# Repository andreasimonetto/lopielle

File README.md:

Lopielle
========

MIDI synth based on Yamaha OPLL FM synthesis sound chip (YM2413).

Made with KiCad, MPLAB-X, Inkscape, The GIMP.

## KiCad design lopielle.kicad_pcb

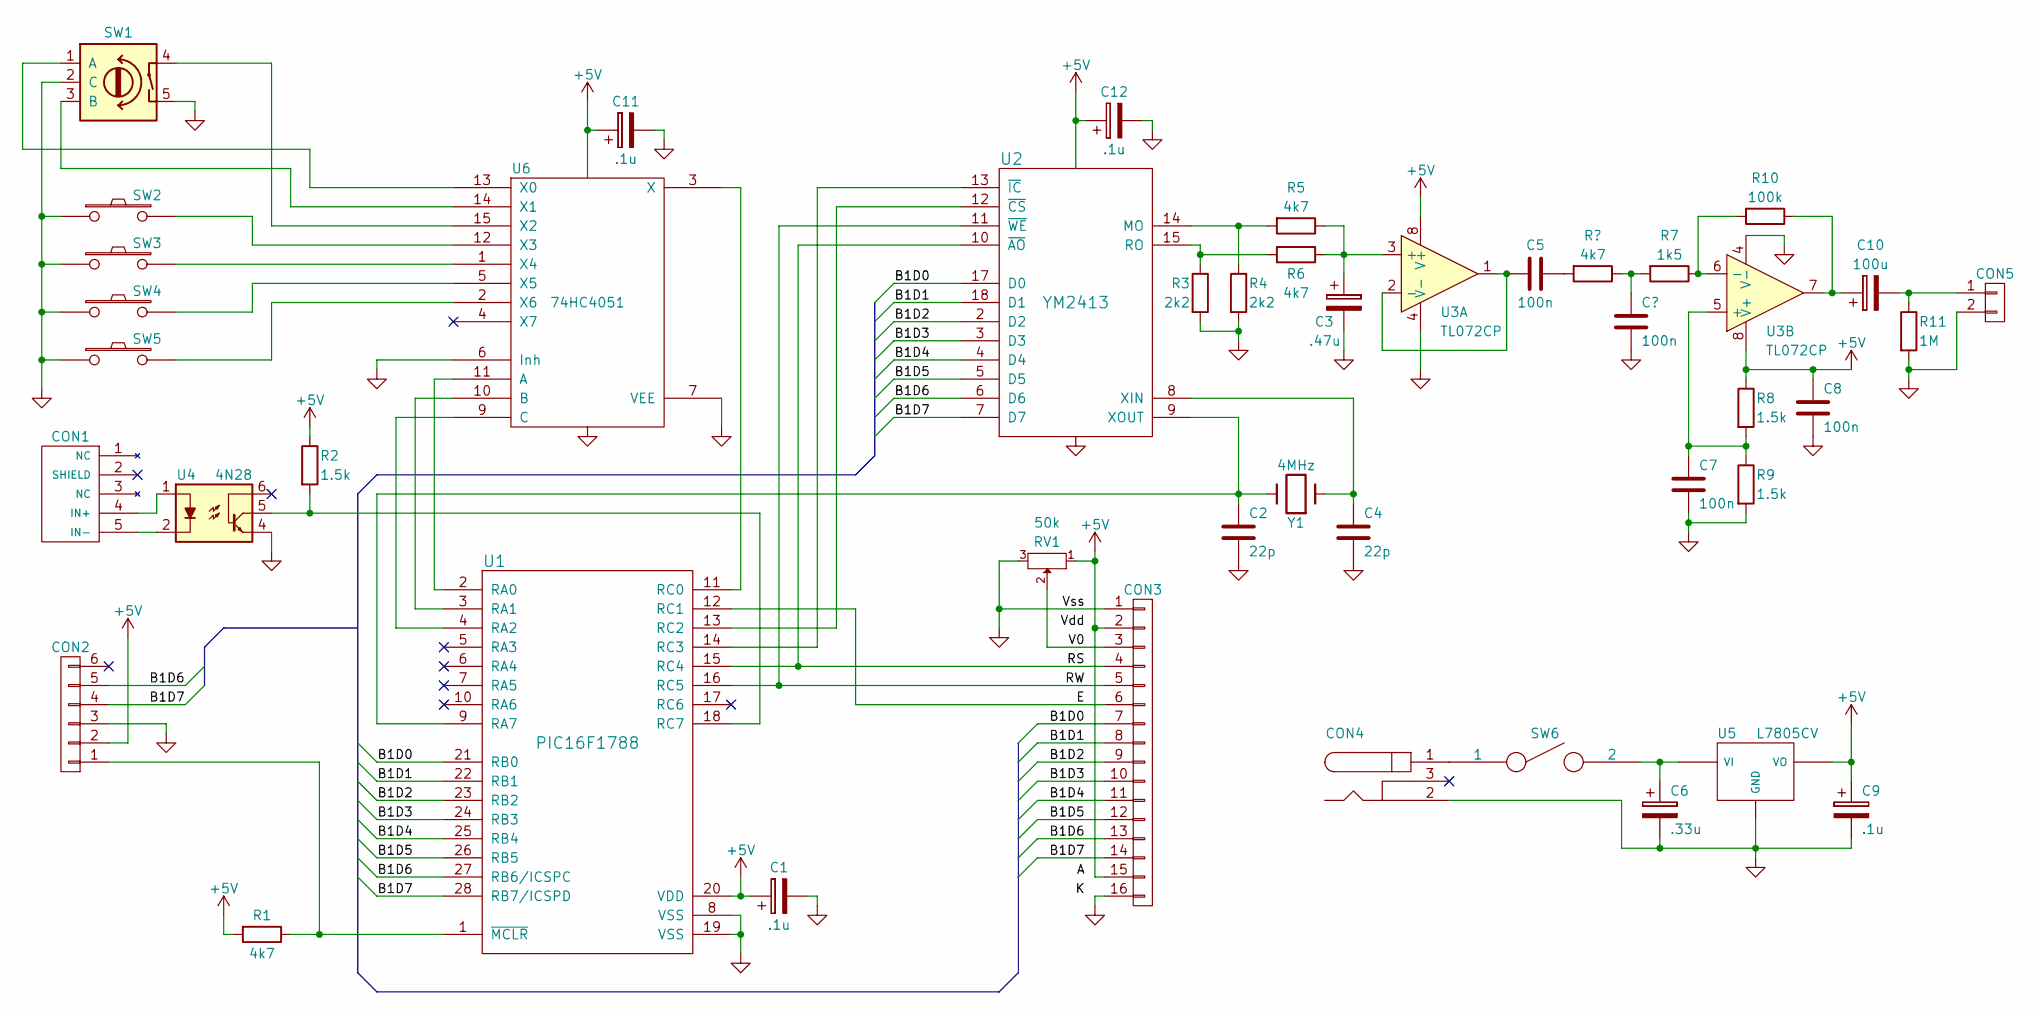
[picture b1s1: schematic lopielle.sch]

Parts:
C1, C9, C11, C12: .1u; C_Radial_D5_L11_P2.5
C2, C4: 22p; C_Disc_D6_P5
C3: .47u; C_Radial_D5_L11_P2.5
C5, C7, C8: 100n; C_Disc_D3_P2.5
C6: .33u; C_Radial_D5_L11_P2.5
C10: 100u; C_Radial_D5_L11_P2.5
CON1: MIDI_In; G9820_SX
CON2: CONN_01X06; PINHEAD1-6
CON3: CONN_01X16; Pin_Header_Straight_1x16
CON4: BARREL_JACK; G10560
CON5: CONN_01X02; Pin_Header_Straight_1x02
R1, R5, R6: 4k7; Resistor_Horizontal_RM7mm
R2, R8, R9: 1.5k; Resistor_Horizontal_RM7mm
R3, R4: 2k2; Resistor_Horizontal_RM7mm
R7: 1k5; Resistor_Horizontal_RM7mm
R10: 100k; Resistor_Horizontal_RM7mm
R11: 1M; Resistor_Horizontal_RM7mm
RV1: 50k; Trimmer_ACP
SW1: Rotary_Encoder_Switch; PEC12R-4222F-S0024
SW2, SW3, SW4, SW5: SW_PUSH; SW_PUSH_SMALL
SW6: SPST; Switch_DPDT
U1: PIC16F1788; DIP-28_W7.62mm
U2: YM2413; DIP-18_W7.62mm
U3: TL072CP; DIP-8_W7.62mm
U4: 4N28; DIP-6_W7.62mm
U5: L7805CV; TO-220_Neutral123_Vertical
U6: 74HC4051; DIP-16_W7.62mm
Y1: 4MHz; Crystal_HC49-U_Vertical

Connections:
+5V: C1.1, C8.1, C9.1, C11.1, C12.1, CON2.2, CON3.2, CON3.15, R1.2, R2.1, R8.1, RV1.1, U1.20 (VDD), U2.16 (VCC), U3.8 (V+), U5.3 (VO), U6.16 (VDD)
/B1D0: CON3.7, U1.21 (RB0), U2.17 (D0)
/B1D1: CON3.8, U1.22 (RB1), U2.18 (D1)
/B1D2: CON3.9, U1.23 (RB2), U2.2 (D2)
/B1D3: CON3.10, U1.24 (RB3), U2.3 (D3)
/B1D4: CON3.11, U1.25 (RB4), U2.4 (D4)
/B1D5: CON3.12, U1.26 (RB5), U2.5 (D5)
/B1D6: CON2.5, CON3.13, U1.27 (RB6/ICSPC), U2.6 (D6)
/B1D7: CON2.4, CON3.14, U1.28 (RB7/ICSPD), U2.7 (D7)
/E: CON3.6, U1.12 (RC1)
/RS: CON3.4, U1.15 (RC4), U2.10 (~AO)
/RW: CON3.5, U1.16 (RC5), U2.11 (~WE)
/V0: CON3.3, RV1.2
GND: C1.2, C2.2, C3.2, C4.2, C6.2, C7.2, C8.2, C9.2, C11.2, C12.2, CON2.3, CON3.1, CON3.16, CON4.2, CON5.2, R3.2, R4.2, R9.2, R11.2, RV1.3, SW1.2 (C), SW1.5, SW2.1, SW3.1, SW4.1, SW5.1, U1.8 (VSS), U1.19 (VSS), U2.1 (GND), U3.4 (V-), U4.4, U5.2 (GND), U6.6 (Inh), U6.7 (VEE), U6.8 (VSS)
unnamed: C2.1, U1.9 (RA7), U2.9 (XOUT), Y1.2
unnamed: C3.1, R5.1, R6.1, U3.3 (+)
unnamed: C4.1, U2.8 (XIN), Y1.1
unnamed: C5.1, R7.2
unnamed: C5.2, U3.1, U3.2 (-)
unnamed: C6.1, SW6.2, U5.1 (VI)
unnamed: C7.1, R8.2, R9.1, U3.5 (+)
unnamed: C10.1, R10.1, U3.7
unnamed: C10.2, CON5.1, R11.1
unnamed: CON1.4 (IN+), U4.1
unnamed: CON1.5 (IN-), U4.2
unnamed: CON2.1, R1.1, U1.1 (~MCLR)
unnamed: CON4.1, SW6.1
unnamed: R2.2, U1.18 (RC7), U4.5
unnamed: R3.1, R6.2, U2.15 (RO)
unnamed: R4.1, R5.2, U2.14 (MO)
unnamed: R7.1, R10.2, U3.6 (-)
unnamed: SW1.1 (A), U6.13 (X0)
unnamed: SW1.3 (B), U6.14 (X1)
unnamed: SW1.4, U6.15 (X2)
unnamed: SW2.2, U6.12 (X3)
unnamed: SW3.2, U6.1 (X4)
unnamed: SW4.2, U6.5 (X5)
unnamed: SW5.2, U6.2 (X6)
unnamed: U1.2 (RA0), U6.11 (A)
unnamed: U1.3 (RA1), U6.10 (B)
unnamed: U1.4 (RA2), U6.9 (C)
unnamed: U1.11 (RC0), U6.3 (X)
unnamed: U1.13 (RC2), U2.12 (~CS)
unnamed: U1.14 (RC3), U2.13 (~IC)

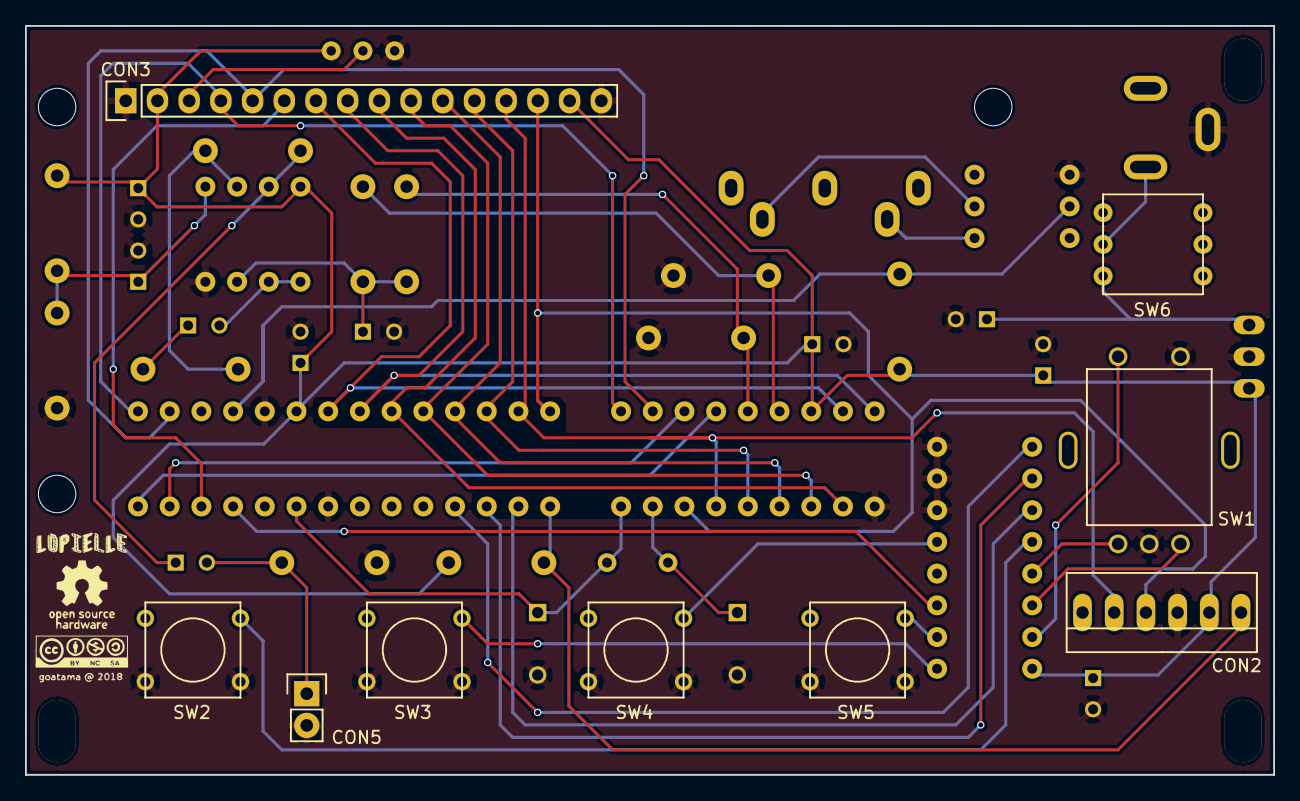
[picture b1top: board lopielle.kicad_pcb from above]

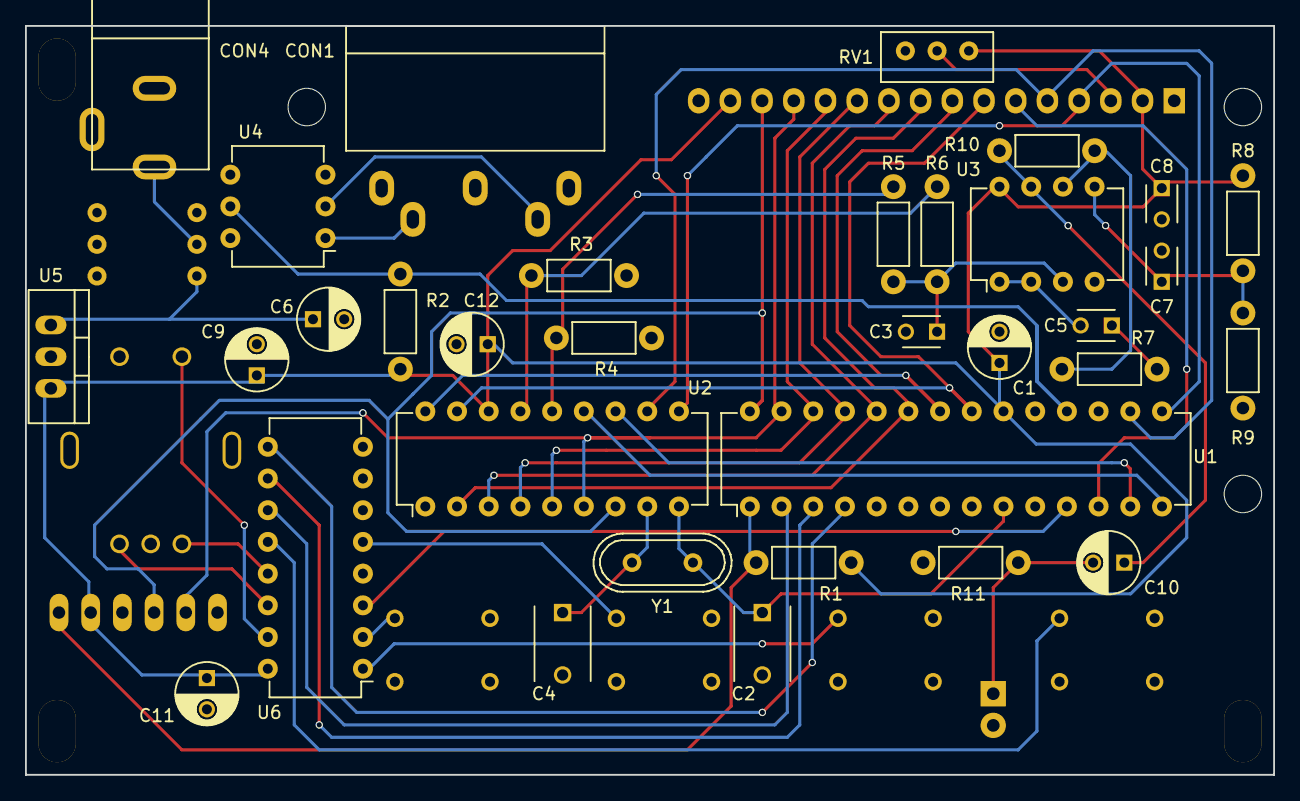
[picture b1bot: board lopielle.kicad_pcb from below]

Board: 2 copper layers, 100.0 x 60.0 mm, 42 parts (33 on the bottom side), 44 nets.

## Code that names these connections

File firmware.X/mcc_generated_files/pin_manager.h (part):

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// get/set CTL_A0 aliases
#define CTL_A0_TRIS                 TRISAbits.TRISA0
#define CTL_A0_LAT                  LATAbits.LATA0
#define CTL_A0_PORT                 PORTAbits.RA0
#define CTL_A0_WPU                  WPUAbits.WPUA0
#define CTL_A0_ANS                  ANSELAbits.ANSA0
#define CTL_A0_SetHigh()            do { LATAbits.LATA0 = 1; } while(0)
#define CTL_A0_SetLow()             do { LATAbits.LATA0 = 0; } while(0)
#define CTL_A0_Toggle()             do { LATAbits.LATA0 = ~LATAbits.LATA0; } while(0)
#define CTL_A0_GetValue()           PORTAbits.RA0
#define CTL_A0_SetDigitalInput()    do { TRISAbits.TRISA0 = 1; } while(0)
#define CTL_A0_SetDigitalOutput()   do { TRISAbits.TRISA0 = 0; } while(0)
#define CTL_A0_SetPullup()          do { WPUAbits.WPUA0 = 1; } while(0)
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// get/set CTL_A1 aliases
#define CTL_A1_TRIS                 TRISAbits.TRISA1
#define CTL_A1_LAT                  LATAbits.LATA1
#define CTL_A1_PORT                 PORTAbits.RA1
#define CTL_A1_WPU                  WPUAbits.WPUA1
#define CTL_A1_ANS                  ANSELAbits.ANSA1
#define CTL_A1_SetHigh()            do { LATAbits.LATA1 = 1; } while(0)
#define CTL_A1_SetLow()             do { LATAbits.LATA1 = 0; } while(0)
#define CTL_A1_Toggle()             do { LATAbits.LATA1 = ~LATAbits.LATA1; } while(0)
#define CTL_A1_GetValue()           PORTAbits.RA1
#define CTL_A1_SetDigitalInput()    do { TRISAbits.TRISA1 = 1; } while(0)
#define CTL_A1_SetDigitalOutput()   do { TRISAbits.TRISA1 = 0; } while(0)
#define CTL_A1_SetPullup()          do { WPUAbits.WPUA1 = 1; } while(0)
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// get/set CTL_A2 aliases
#define CTL_A2_TRIS                 TRISAbits.TRISA2
#define CTL_A2_LAT                  LATAbits.LATA2
#define CTL_A2_PORT                 PORTAbits.RA2
#define CTL_A2_WPU                  WPUAbits.WPUA2
#define CTL_A2_ANS                  ANSELAbits.ANSA2
#define CTL_A2_SetHigh()            do { LATAbits.LATA2 = 1; } while(0)
#define CTL_A2_SetLow()             do { LATAbits.LATA2 = 0; } while(0)
#define CTL_A2_Toggle()             do { LATAbits.LATA2 = ~LATAbits.LATA2; } while(0)
#define CTL_A2_GetValue()           PORTAbits.RA2
#define CTL_A2_SetDigitalInput()    do { TRISAbits.TRISA2 = 1; } while(0)
#define CTL_A2_SetDigitalOutput()   do { TRISAbits.TRISA2 = 0; } while(0)
#define CTL_A2_SetPullup()          do { WPUAbits.WPUA2 = 1; } while(0)
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// get/set D0 aliases
#define D0_TRIS                 TRISBbits.TRISB0
#define D0_LAT                  LATBbits.LATB0
#define D0_PORT                 PORTBbits.RB0
#define D0_WPU                  WPUBbits.WPUB0
#define D0_ANS                  ANSELBbits.ANSB0
#define D0_SetHigh()            do { LATBbits.LATB0 = 1; } while(0)
#define D0_SetLow()             do { LATBbits.LATB0 = 0; } while(0)
#define D0_Toggle()             do { LATBbits.LATB0 = ~LATBbits.LATB0; } while(0)
#define D0_GetValue()           PORTBbits.RB0
#define D0_SetDigitalInput()    do { TRISBbits.TRISB0 = 1; } while(0)
#define D0_SetDigitalOutput()   do { TRISBbits.TRISB0 = 0; } while(0)
#define D0_SetPullup()          do { WPUBbits.WPUB0 = 1; } while(0)
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// get/set D1 aliases
#define D1_TRIS                 TRISBbits.TRISB1
#define D1_LAT                  LATBbits.LATB1
#define D1_PORT                 PORTBbits.RB1
#define D1_WPU                  WPUBbits.WPUB1
#define D1_ANS                  ANSELBbits.ANSB1
#define D1_SetHigh()            do { LATBbits.LATB1 = 1; } while(0)
#define D1_SetLow()             do { LATBbits.LATB1 = 0; } while(0)
#define D1_Toggle()             do { LATBbits.LATB1 = ~LATBbits.LATB1; } while(0)
#define D1_GetValue()           PORTBbits.RB1
#define D1_SetDigitalInput()    do { TRISBbits.TRISB1 = 1; } while(0)
#define D1_SetDigitalOutput()   do { TRISBbits.TRISB1 = 0; } while(0)
#define D1_SetPullup()          do { WPUBbits.WPUB1 = 1; } while(0)
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// get/set D2 aliases
#define D2_TRIS                 TRISBbits.TRISB2
#define D2_LAT                  LATBbits.LATB2
#define D2_PORT                 PORTBbits.RB2
#define D2_WPU                  WPUBbits.WPUB2
#define D2_ANS                  ANSELBbits.ANSB2
#define D2_SetHigh()            do { LATBbits.LATB2 = 1; } while(0)
#define D2_SetLow()             do { LATBbits.LATB2 = 0; } while(0)
#define D2_Toggle()             do { LATBbits.LATB2 = ~LATBbits.LATB2; } while(0)
#define D2_GetValue()           PORTBbits.RB2
#define D2_SetDigitalInput()    do { TRISBbits.TRISB2 = 1; } while(0)
#define D2_SetDigitalOutput()   do { TRISBbits.TRISB2 = 0; } while(0)
#define D2_SetPullup()          do { WPUBbits.WPUB2 = 1; } while(0)
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// get/set D3 aliases
#define D3_TRIS                 TRISBbits.TRISB3
#define D3_LAT                  LATBbits.LATB3
#define D3_PORT                 PORTBbits.RB3
#define D3_WPU                  WPUBbits.WPUB3
#define D3_ANS                  ANSELBbits.ANSB3
#define D3_SetHigh()            do { LATBbits.LATB3 = 1; } while(0)
#define D3_SetLow()             do { LATBbits.LATB3 = 0; } while(0)
#define D3_Toggle()             do { LATBbits.LATB3 = ~LATBbits.LATB3; } while(0)
#define D3_GetValue()           PORTBbits.RB3
#define D3_SetDigitalInput()    do { TRISBbits.TRISB3 = 1; } while(0)
#define D3_SetDigitalOutput()   do { TRISBbits.TRISB3 = 0; } while(0)
#define D3_SetPullup()          do { WPUBbits.WPUB3 = 1; } while(0)
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// get/set D4 aliases
#define D4_TRIS                 TRISBbits.TRISB4
#define D4_LAT                  LATBbits.LATB4
#define D4_PORT                 PORTBbits.RB4
#define D4_WPU                  WPUBbits.WPUB4
#define D4_ANS                  ANSELBbits.ANSB4
#define D4_SetHigh()            do { LATBbits.LATB4 = 1; } while(0)
#define D4_SetLow()             do { LATBbits.LATB4 = 0; } while(0)
#define D4_Toggle()             do { LATBbits.LATB4 = ~LATBbits.LATB4; } while(0)
#define D4_GetValue()           PORTBbits.RB4
#define D4_SetDigitalInput()    do { TRISBbits.TRISB4 = 1; } while(0)
#define D4_SetDigitalOutput()   do { TRISBbits.TRISB4 = 0; } while(0)
#define D4_SetPullup()          do { WPUBbits.WPUB4 = 1; } while(0)
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// get/set D5 aliases
#define D5_TRIS                 TRISBbits.TRISB5
#define D5_LAT                  LATBbits.LATB5
#define D5_PORT                 PORTBbits.RB5
#define D5_WPU                  WPUBbits.WPUB5
#define D5_ANS                  ANSELBbits.ANSB5
#define D5_SetHigh()            do { LATBbits.LATB5 = 1; } while(0)
#define D5_SetLow()             do { LATBbits.LATB5 = 0; } while(0)
#define D5_Toggle()             do { LATBbits.LATB5 = ~LATBbits.LATB5; } while(0)
#define D5_GetValue()           PORTBbits.RB5
#define D5_SetDigitalInput()    do { TRISBbits.TRISB5 = 1; } while(0)
#define D5_SetDigitalOutput()   do { TRISBbits.TRISB5 = 0; } while(0)
#define D5_SetPullup()          do { WPUBbits.WPUB5 = 1; } while(0)
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// get/set D6 aliases
#define D6_TRIS                 TRISBbits.TRISB6
#define D6_LAT                  LATBbits.LATB6
#define D6_PORT                 PORTBbits.RB6
#define D6_WPU                  WPUBbits.WPUB6
#define D6_ANS                  ANSELBbits.ANSB6
#define D6_SetHigh()            do { LATBbits.LATB6 = 1; } while(0)
#define D6_SetLow()             do { LATBbits.LATB6 = 0; } while(0)
#define D6_Toggle()             do { LATBbits.LATB6 = ~LATBbits.LATB6; } while(0)
#define D6_GetValue()           PORTBbits.RB6
#define D6_SetDigitalInput()    do { TRISBbits.TRISB6 = 1; } while(0)
#define D6_SetDigitalOutput()   do { TRISBbits.TRISB6 = 0; } while(0)
#define D6_SetPullup()          do { WPUBbits.WPUB6 = 1; } while(0)
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// get/set D7 aliases
#define D7_TRIS                 TRISBbits.TRISB7
#define D7_LAT                  LATBbits.LATB7
#define D7_PORT                 PORTBbits.RB7
#define D7_WPU                  WPUBbits.WPUB7
#define D7_SetHigh()            do { LATBbits.LATB7 = 1; } while(0)
#define D7_SetLow()             do { LATBbits.LATB7 = 0; } while(0)
#define D7_Toggle()             do { LATBbits.LATB7 = ~LATBbits.LATB7; } while(0)
#define D7_GetValue()           PORTBbits.RB7
#define D7_SetDigitalInput()    do { TRISBbits.TRISB7 = 1; } while(0)
#define D7_SetDigitalOutput()   do { TRISBbits.TRISB7 = 0; } while(0)
#define D7_SetPullup()          do { WPUBbits.WPUB7 = 1; } while(0)
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// get/set CTL_DATA aliases
#define CTL_DATA_TRIS                 TRISCbits.TRISC0
#define CTL_DATA_LAT                  LATCbits.LATC0
#define CTL_DATA_PORT                 PORTCbits.RC0
#define CTL_DATA_WPU                  WPUCbits.WPUC0
#define CTL_DATA_ANS                  ANSELCbits.ANSC0
#define CTL_DATA_SetHigh()            do { LATCbits.LATC0 = 1; } while(0)
#define CTL_DATA_SetLow()             do { LATCbits.LATC0 = 0; } while(0)
#define CTL_DATA_Toggle()             do { LATCbits.LATC0 = ~LATCbits.LATC0; } while(0)
#define CTL_DATA_GetValue()           PORTCbits.RC0
#define CTL_DATA_SetDigitalInput()    do { TRISCbits.TRISC0 = 1; } while(0)
#define CTL_DATA_SetDigitalOutput()   do { TRISCbits.TRISC0 = 0; } while(0)
#define CTL_DATA_SetPullup()          do { WPUCbits.WPUC0 = 1; } while(0)
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// get/set DPY_CS aliases
#define DPY_CS_TRIS                 TRISCbits.TRISC1
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
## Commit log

2018-12-04 Added base project files
2018-12-07 Paths fix

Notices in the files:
firmware.X/mcc_generated_files/pin_manager.h:
(c) 2018 Microchip Technology Inc. and its subsidiaries.
lopielle.sch:
CC BY-NC-SA 3.0
